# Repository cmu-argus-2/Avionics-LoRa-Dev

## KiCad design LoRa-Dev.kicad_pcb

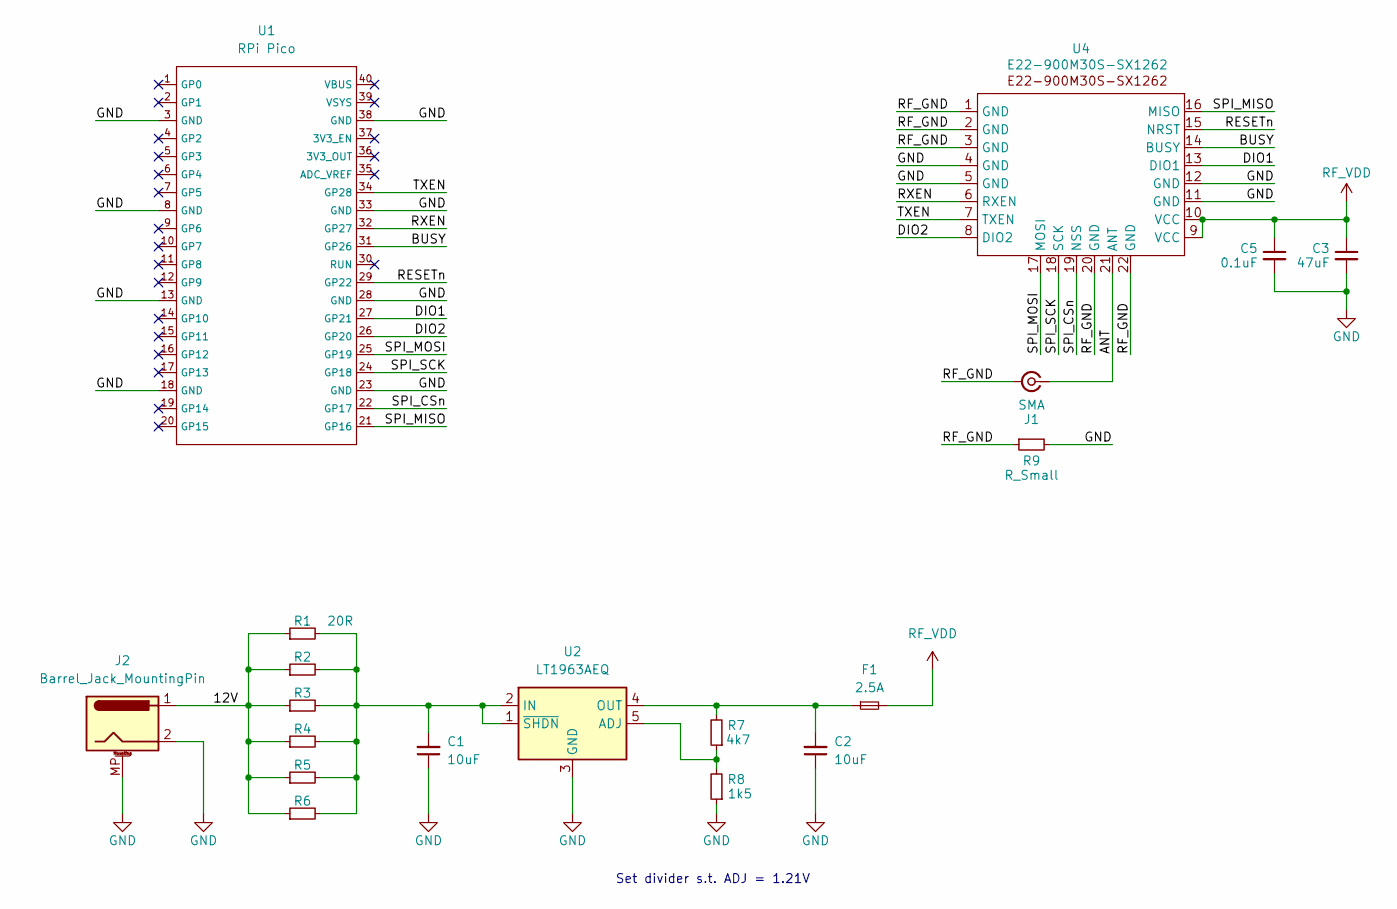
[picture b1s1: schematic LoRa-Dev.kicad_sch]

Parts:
C1, C2: 10uF; C_1210_3225Metric
C3: 47uF; C_1210_3225Metric
C5: 0.1uF; C_0603_1608Metric
F1: 2.5A; Fuse_0805_2012Metric
J1: SMA; SMA_Amphenol_901-144_Vertical
J2: Barrel_Jack_MountingPin; BarrelJack_CUI_PJ-063AH_Horizontal
R1, R2, R3, R4, R5, R6: 20R; R_2512_6332Metric
R7: 4k7; R_0603_1608Metric
R8: 1k5; R_0603_1608Metric
R9: R_Small; R_0603_1608Metric
U1: RPi Pico; RPi_Pico
U2: LT1963AEQ; TO-263-5_TabPin3
U4: E22-900M30S-SX1262

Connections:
/12V: J2.1, R1.1, R2.1, R3.1, R4.1, R5.1, R6.1
/ANT: J1.1 (In), U4.21 (ANT)
/BUSY: U1.31 (GP26), U4.14 (BUSY)
/DIO1: U1.27 (GP21), U4.13 (DIO1)
/DIO2: U1.26 (GP20), U4.8 (DIO2)
/RESETn: U1.29 (GP22), U4.15 (NRST)
/RF_GND: J1.2 (Ext), R9.1, U4.1 (GND), U4.2 (GND), U4.3 (GND), U4.20 (GND), U4.22 (GND)
/RXEN: U1.32 (GP27), U4.6 (RXEN)
/SPI_CSn: U1.22 (GP17), U4.19 (NSS)
/SPI_MISO: U1.21 (GP16), U4.16 (MISO)
/SPI_MOSI: U1.25 (GP19), U4.17 (MOSI)
/SPI_SCK: U1.24 (GP18), U4.18 (SCK)
/TXEN: U1.34 (GP28), U4.7 (TXEN)
GND: C1.1, C2.1, C3.2, C5.2, J2.2, J2.MP (MountPin), R8.1, R9.2, U1.3 (GND), U1.8 (GND), U1.13 (GND), U1.18 (GND), U1.23 (GND), U1.28 (GND), U1.33 (GND), U1.38 (GND), U2.3 (GND), U4.4 (GND), U4.5 (GND), U4.11 (GND), U4.12 (GND)
unnamed: R7.1, R8.2, U2.5 (ADJ)
unnamed: C1.2, R1.2, R2.2, R3.2, R4.2, R5.2, R6.2, U2.1 (~SHDN), U2.2 (IN)
unnamed: C2.2, F1.1, R7.2, U2.4 (OUT)
RF_VDD: C3.1, C5.1, F1.2, U4.9 (VCC), U4.10 (VCC)

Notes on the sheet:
Set divider s.t. ADJ = 1.21V

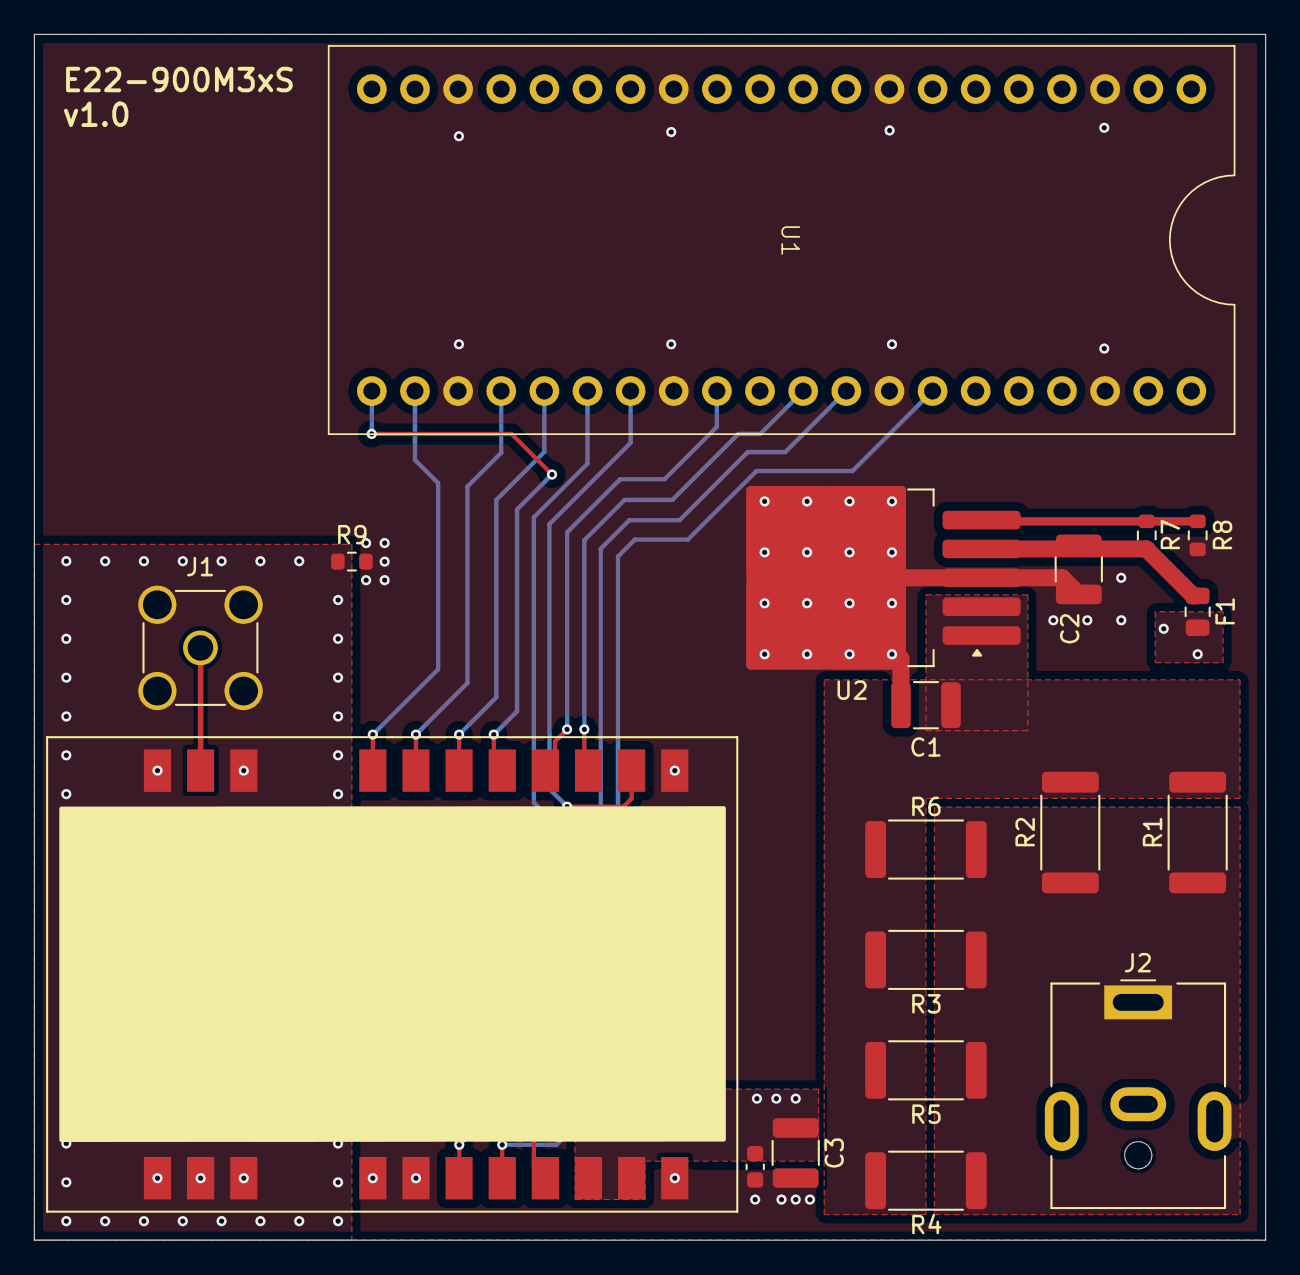
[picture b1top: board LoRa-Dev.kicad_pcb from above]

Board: 4 copper layers, 72.5 x 71.0 mm, 19 parts (0 on the bottom side), 18 nets.

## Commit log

2024-09-27 Init submodules
2024-09-27 Base board
2024-09-28 board layout
2024-09-29 RFM95W
2024-09-29 Update silkscreen
2024-09-29 Added board id
2024-09-30 Updated RF GND
2024-09-30 Actually fixed RF GND
2024-09-30 Repoured poly
2024-09-30 RFM95PW wrong branch name
2024-09-30 E22-900M30S
2024-09-30 fixed
2024-09-30 Fixed minor layout issues
2024-09-30 updated after first review
2024-10-01 Minor fixes, exported BOM
2024-10-02 Some fixes, exported BOM
